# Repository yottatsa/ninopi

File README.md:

# ninopi

NinoTNC to Raspberry Pi integration board

[NinoTNC](https://tarpn.net/t/nino-tnc/nino-tnc.html) is 300-9600 baud multi-mode packet radio KISS TNC by [Nino Carrillo](https://github.com/ninocarrillo). This board bypassed provided USB-serial interface and uses rpi internal one.

This board also provides with [Recon 12V DC-DC converter](https://www.recom-power.com/pdf/Innoline/RPM-6.0.pdf) to power the rig from the same power rail, RPi and PoE headers pass-thru, Wi-Fi antenna mount, and simple fan PWM controller.

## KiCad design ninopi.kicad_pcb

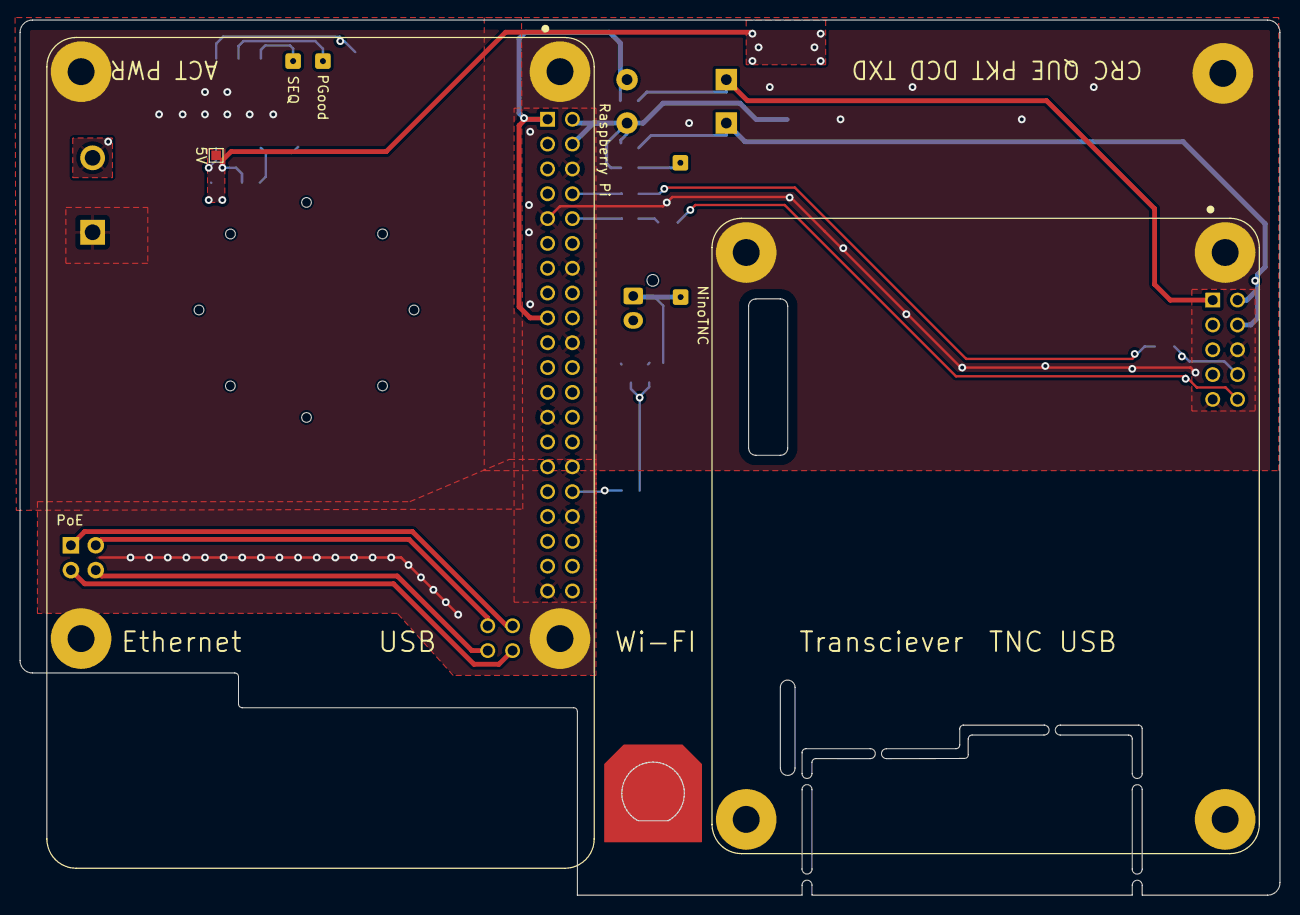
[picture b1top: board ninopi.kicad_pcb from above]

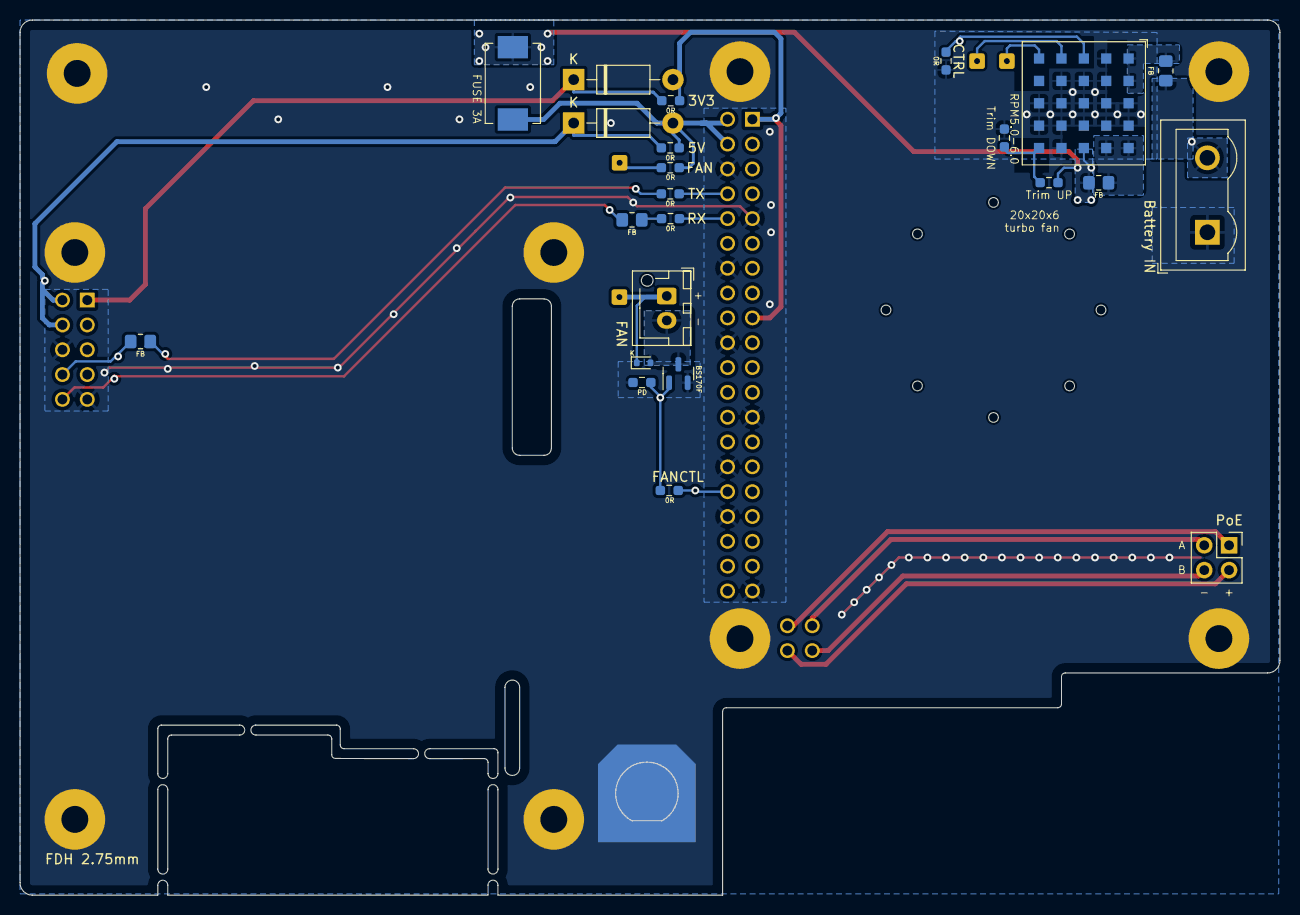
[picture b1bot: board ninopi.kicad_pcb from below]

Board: 2 copper layers, 128.9 x 89.5 mm, 29 parts (23 on the bottom side), 27 nets.

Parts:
5V: TestPoint_Pad_1.0x1.0mm
D1, D2: 1N4001; D_DO-41_SOD81_P10.16mm_Horizontal
D3: 1N4148WT; D_SOD-523
F2: FUSE 3A; Fuse_Bourns_MF-SM_7.98x5.44mm
FB1, FB2, FB3, FB4: FB; R_0805_2012Metric_Pad1.20x1.40mm_HandSolder
H1: Wi-Fi; SMARP
J1: Raspberry Pi; MODULE_RASPBERRY_PI_3_MODEL_B_
J2: NinoTNC; SMT_TARPN_NinoTNC
J3: PoE; PinSocket_2x02_P2.54mm_Vertical
J4: FAN; JST_XH_B2B-XH-AM_1x02_P2.50mm_Vertical
J5: Battery IN; TerminalBlock_Wuerth_691311400102_P7.62mm
Q1: BS170F; SOT-23
R1: TX; R_0603_1608Metric_Pad0.98x0.95mm_HandSolder
R2: RX; R_0603_1608Metric_Pad0.98x0.95mm_HandSolder
R3, R4, R5, R7: 0R; R_0603_1608Metric_Pad0.98x0.95mm_HandSolder
R6: PD; R_0603_1608Metric_Pad0.98x0.95mm_HandSolder
R8: CTRL; R_0603_1608Metric_Pad0.98x0.95mm_HandSolder
R9: Trim DOWN; R_0603_1608Metric_Pad0.98x0.95mm_HandSolder
R10: Trim UP; R_0603_1608Metric_Pad0.98x0.95mm_HandSolder
TP1: SEQ; SolderWire-0.1sqmm_1x01_D0.4mm_OD1mm
TP2: PGood; SolderWire-0.1sqmm_1x01_D0.4mm_OD1mm
U1: RPM5.0-6.0; Converter_DCDC_RECOM_RPMx.x-x.0

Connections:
3V3: D1.2 (A), J1.1 (3V3), J1.17 (3V3), R3.1
5V: D2.2 (A), F2.1, J1.2 (5V), J1.4 (5V), R4.2, R5.1
/5V.H1: FB2.1, U1.A5 (+VOUT), U1.B5 (+VOUT)
/FAN: D3.1 (K), J4.1, R5.2
/FANFET: D3.2 (A), J4.2, Q1.3 (D)
/TNC.3V3: D1.1 (K), J2.1 (3V3), R3.2
/TNC.5V: D2.1 (K), J2.2 (5V), J2.4 (5V), R4.1
/TR00: J1.44 (TR00), J3.1
/TR01: J1.43 (TR01), J3.2
/TR02: J1.42 (TR02), J3.3
/TR03: J1.41 (TR03), J3.4
FAN.PWM: J1.32 (PWM0/GPIO12), R7.1
GND: H1.GND, J1.6 (GND), J1.9 (GND), J1.14 (GND), J1.20 (GND), J1.25 (GND), J1.30 (GND), J1.34 (GND), J1.39 (GND), J2.6 (GND), J2.9 (GND), J5.1, Q1.2 (S), R6.1, R8.1, R9.1, U1.A3 (GND), U1.A4 (GND), U1.B1 (GND), U1.B2 (GND), U1.B3 (GND), U1.B4 (GND), U1.C2 (GND), U1.C3 (GND), U1.C4 (GND), U1.D2 (GND), U1.D3 (GND), U1.D4 (GND), U1.D5 (GND), U1.E3 (GND), U1.E4 (GND)
unnamed: FB1.2, U1.A1 (+VIN), U1.A2 (+VIN)
unnamed: FB3.2, R1.1
unnamed: FB4.2, R2.1
unnamed: FB4.1, J2.10 (RX)
unnamed: FB3.1, J2.8 (TX)
unnamed: Q1.1 (G), R6.2, R7.2
unnamed: R8.2, U1.C1 (CTRL)
unnamed: TP2.1, U1.D1 (PGood)
unnamed: TP1.1, U1.E1 (SEQ)
PWRTRIM: R9.2, R10.1, U1.E5 (Trim)
SENSE: F2.2, FB2.2, R10.2, U1.C5 (Sense)
UART0_RX: J1.10 (GPIO15/RXD), R2.2
UART0_TX: J1.8 (GPIO14/TXD), R1.2
VIN: FB1.1, J5.2

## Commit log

2024-05-06 initial
